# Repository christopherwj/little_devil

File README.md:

## Welcome to GitHub Pages

You can use the [editor on GitHub](https://github.com/christopherwj/little_devil/edit/master/README.md) to maintain and preview the content for your website in Markdown files.

Whenever you commit to this repository, GitHub Pages will run [Jekyll](https://jekyllrb.com/) to rebuild the pages in your site, from the content in your Markdown files.

### Markdown

Markdown is a lightweight and easy-to-use syntax for styling your writing. It includes conventions for

```markdown
Syntax highlighted code block

# Header 1
## Header 2
### Header 3

- Bulleted
- List

1. Numbered
2. List

**Bold** and _Italic_ and `Code` text

[Link](url) and 
```

For more details see [GitHub Flavored Markdown](https://guides.github.com/features/mastering-markdown/).

### Jekyll Themes

Your Pages site will use the layout and styles from the Jekyll theme you have selected in your [repository settings](https://github.com/christopherwj/little_devil/settings). The name of this theme is saved in the Jekyll `_config.yml` configuration file.

### Support or Contact

Having trouble with Pages? Check out our [documentation](https://help.github.com/categories/github-pages-basics/) or [contact support](https://github.com/contact) and we’ll help you sort it out.

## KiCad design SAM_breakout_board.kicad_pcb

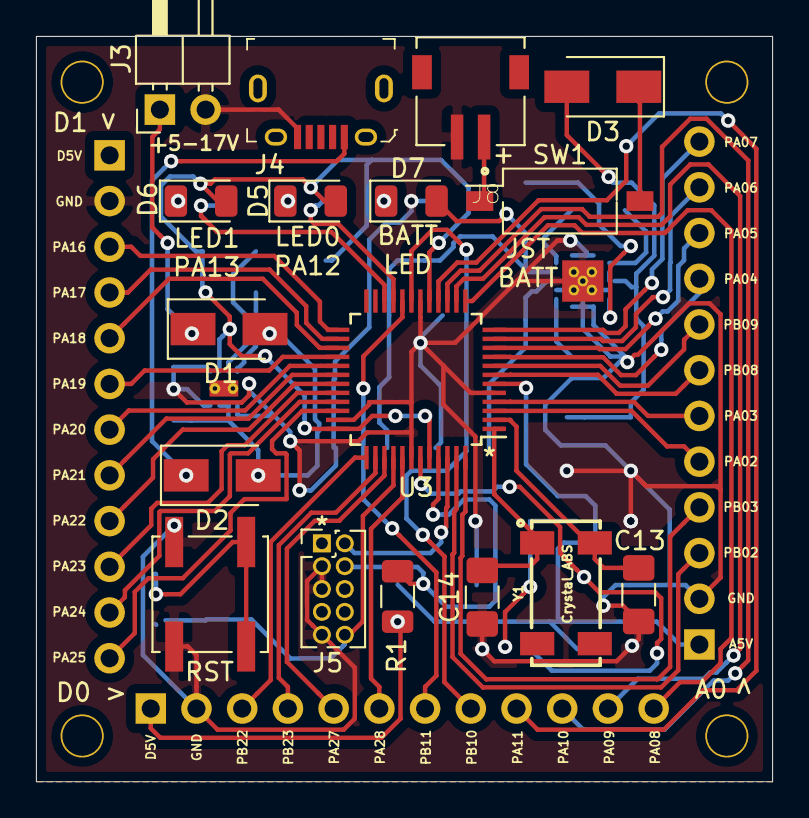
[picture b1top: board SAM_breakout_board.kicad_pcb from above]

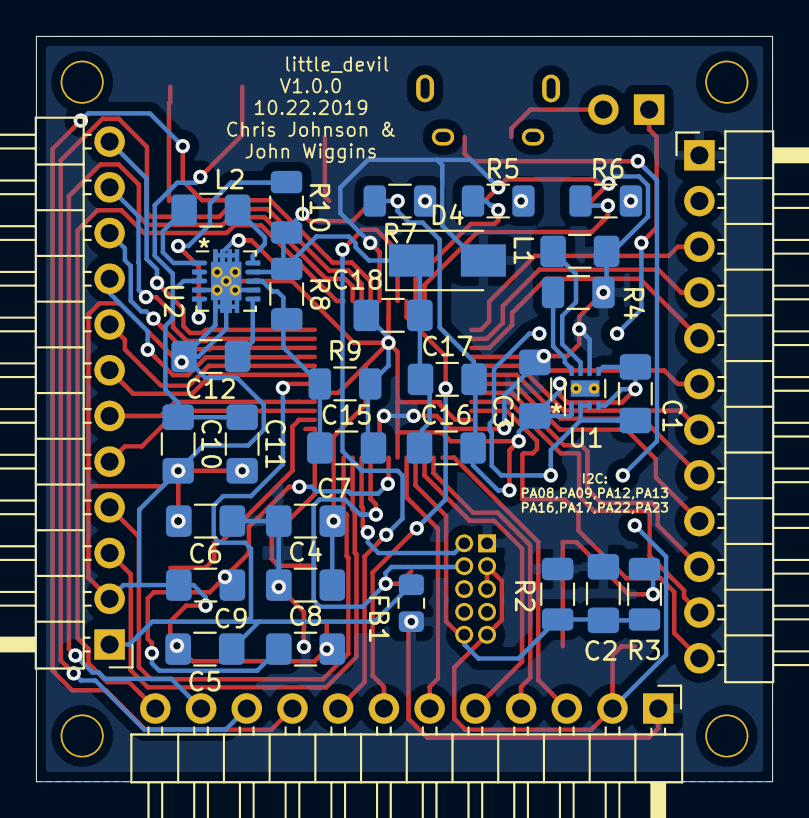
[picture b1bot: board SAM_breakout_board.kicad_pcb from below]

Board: 2 copper layers, 40.9 x 41.4 mm, 51 parts (34 on the bottom side), 59 nets.

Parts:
C1, C4, C5, C10, C11: 10uF; C_1206_3216Metric_Pad1.42x1.75mm_HandSolder
C2: 100pF; C_1206_3216Metric_Pad1.42x1.75mm_HandSolder
C3, C16, C17, C18: 22uF; C_1206_3216Metric_Pad1.42x1.75mm_HandSolder
C6, C7, C9: 100nF; C_1206_3216Metric_Pad1.42x1.75mm_HandSolder
C8: 1uF; C_1206_3216Metric_Pad1.42x1.75mm_HandSolder
C12: 0.1uF; C_1206_3216Metric_Pad1.42x1.75mm_HandSolder
C13, C14: 15pF; C_1206_3216Metric_Pad1.42x1.75mm_HandSolder
C15: 10pF; C_1206_3216Metric_Pad1.42x1.75mm_HandSolder
D1, D2, D3, D4: B160-13-F; D_SMA
D5, D6, D7: LED; LED_1206_3216Metric
FB1: Ferrite_Bead_Small; L_0805_2012Metric_Pad1.15x1.40mm_HandSolder
J3: Conn_01x02; PinHeader_1x02_P2.54mm_Horizontal
J4: USB_B_Micro; USB_Micro_B_Female_10118194-0001LF
J5: Conn_ARM_JTAG_SWD_10; PinHeader_2x05_P1.27mm_Vertical
J8: Conn_01x02; JST_S2B-ZR-SM4A-TF(LF)(SN)
J9, J10, J11: Conn_01x12; PinHeader_1x12_P2.54mm_Horizontal
L1: 2.2uH; L_1206_3216Metric_Pad1.42x1.75mm_HandSolder
L2: 1uH; L_1206_3216Metric_Pad1.42x1.75mm_HandSolder
R1: 1k; R_1206_3216Metric
R2: 2.2k; R_1206_3216Metric
R3: 330; R_1206_3216Metric
R4: 100k; R_1206_3216Metric
R5, R6, R7: 240; R_1206_3216Metric
R8, R10: 1M; R_1206_3216Metric
R9: 111k; R_1206_3216Metric
RST: RST_SW; SW_Push_1P1T_NO_CK_KSC6xxJ
SW1: BATT_PWR; SW_DIP_SPSTx01_Slide_Omron_A6S-110x_W8.9mm_P2.54mm
U1: TPS62163DSG; WSON-8-1EP_2x2mm_P0.5mm_EP0.9x1.6mm_ThermalVias
U2: TPS63060; Texas_S-PWSON-N10_ThermalVias
U3: ATSAMD21G18A-AUT; TQFP-48_7x7mm_P0.5mm
Y1: Crystal_ABS; SOJ-4

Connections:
5V_BATT: C16.1, C17.1, C18.1, D4.1, D7.2, R8.1, R10.2, U2.9
GND: C1.2, C3.2, C4.2, C5.2, C6.2, C7.2, C8.2, C9.2, C10.2, C11.2, C12.2, C13.2, C14.1, C15.2, C16.2, C17.2, C18.2, J3.2, J4.5, J5.3, J5.5, J5.9, J8.2, J9.2, J10.2, J11.2, R7.2, R9.2, RST.1, U1.1, U1.4, U1.5, U2.4, U2.7, U2.11, U3.5, U3.18, U3.35, U3.42
LED0: R5.2, U3.21
LED1: R6.2, U3.22
unnamed: C1.1, D1.2, D2.2, U1.2, U1.3
unnamed: C12.1, U2.6
unnamed: C13.1, U3.2, Y1.4
unnamed: C14.2, U3.1, Y1.1
unnamed: C15.1, R8.2, R9.1, U2.8
unnamed: D1.1, J3.1
unnamed: D2.1, J4.1
unnamed: D3.1, SW1.2
unnamed: D5.1, R5.1
unnamed: D6.1, R6.1
unnamed: D7.1, R7.1
unnamed: J8.1, SW1.1
unnamed: L1.2, U1.7
unnamed: L2.1, U2.1
unnamed: L2.2, U2.10
unnamed: R3.2, RST.2
unnamed: R4.1, U1.8
unnamed: R10.1, U2.5
PA02: J9.5, U3.3
PA03: J9.6, U3.4
PA04: J9.9, U3.9
PA05: J9.10, U3.10
PA06: J9.11, U3.11
PA07: J9.12, U3.12
PA08: J10.12, U3.13
PA09: J10.11, U3.14
PA10: J10.10, U3.15
PA11: J10.9, U3.16
PA16: J11.3, U3.25
PA17: J11.4, U3.26
PA18: J11.5, U3.27
PA19: J11.6, U3.28
PA20: J11.7, U3.29
PA21: J11.8, U3.30
PA22: J11.9, U3.31
PA23: J11.10, U3.32
PA24: J11.11, U3.33
PA25: J11.12, U3.34
PA27: J10.5, U3.39
PA28: J10.6, U3.41
PB02: J9.3, U3.47
PB03: J9.4, U3.48
PB08: J9.7, U3.7
PB09: J9.8, U3.8
PB10: J10.8, U3.19
PB11: J10.7, U3.20
PB22: J10.3, U3.37
PB23: J10.4, U3.38
RST: C2.2, J5.10, R2.2, R3.1, U3.40
SWCLK: J5.4, R1.2, U3.45
SWDIO: J5.2, U3.46
VDDANA: C5.1, FB1.1, J9.1, U3.6
VDDCORE: C8.1, C9.1, U3.43
VDDIN: C2.1, C3.1, C4.1, C6.1, C7.1, D4.2, D5.2, D6.2, FB1.2, J5.1, J10.1, J11.1, L1.1, R1.1, R2.1, R4.2, U1.6, U3.17, U3.36, U3.44
V_BATT: C10.1, C11.1, D3.2, U2.2, U2.3

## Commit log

2019-10-12 Added Documentation for related parts
    Stores related project material.
2019-10-12 Delete Documentation
    Created file instead of directory by mistake.
2019-10-12 Initial Push
    Created necessary files as needed populated schematic 90%.
    Schematic still needs GPIO pin symbols made and assigned.
    Project:
    Need to finish schematic.
    Generate Netlist
    Place components
2019-10-12 Added 4 GPIO Auxillary Rails
    Added 4 sets of 4 auxillary rails that provide a way to easily probe
    any routed connection.
    For example, if someone wants to see the data being transmitted on a SCL
    line during I2C communication, they have a floating rail to connect a
    probe to during comms.
2019-10-13 Associated most footprints with symbols
    Documentation:
    Added SAMC21 data sheet.
    schematic:
    Added 3 GPIO rows for board.
    Annotated.
    Next steps:
2019-10-13 Began board layout
    Added footprints for power switches and SAM programming pins
    Added footprints for JST and uUSB header
    Created optional board layout using a 75mm square as the starting size,
    going to give 50mm a try in next edit.
2019-10-13 Set theme jekyll-theme-midnight
2019-10-20 Modification of footprints
    Modified the footprints of the programmer header to be the correct pitch
    Changed the JST connector to a generic 2 pin connector. The pitch of the
    JST connector for it did not exist as a footprint, so chose one that fit
    the online options. Further verification is needed for this.
2019-10-20 Additional JST footprint library
    Updated the battery connection with appropriate footprint library
    Added library for that part that was downloaded to the footprints folder
2019-10-20 Footprint not applied error
    Caught an error with the footprint not being applied to the JST
    connection for the batter, corrected.
    Footprint change before was not saved before push.
2019-10-21 Changed Wiring
    Changed the tracing in several different areas
    moving conflicting components around to avoid conflicts of footprints
    Need to:
    remove aux rails
    update footprints on power inputs
    check circuitry to make sure routing is correct
2019-10-26 Rearranged layout completely
    Board is done with the exception of validation.
    PCB will be in on 10/28/2019.
    Added a BOM for ordering, will be continually modifying as needed.
2019-10-27 Added PDF of Schematic
    Added a pdf of schematic to documentation folder for easier viewing of
    circuitry.
2019-10-27 Added BOM in Documentation
    Added the ordering BOM in documentation so that we know all of what we
    ordered and from where. Total for ordering for 5 boards came out to ~$150 for everything.
